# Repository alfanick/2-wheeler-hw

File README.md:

# TwoWheeler
TwoWheeler is Self Balancing Robot implemented using [XMOS startKIT](http://www.xmos.com/startkit) platform.

The robot is solving physical problem of inverted pendulum using PID regulator connecting motors with accelerometer. However its hardware design has much more features:
* 8 core 32-bit microcontroller
* bluetooth transceiver
* two distance meters
* motor driver with current sensing
* buck converter designed for use with LiPo battery
* battery voltage monitoring
* Over-The-Air parameters programming to built-in flash
* high torque motors with encoders

## Parts

* XMOS firmware - more in [balancer README](sw_twowheeler/app_balancer/README.md)
* computer app - API available in Ruby and console command interface with scripting (more in [documentation](ruby_twowheeler/README.md))
* circuit schematic and PCB design
* hardware design - not yet documented

## Authors

* Amadeusz Juskowiak - amadeusz@me.com
* Piotr Żurkowski  - kareth92@gmail.com

Inspired by Embedded Systems course at Poznan University of
Technology.

## License

*Copyright 2014 Amadeusz Juskowiak*

Licensed under the Apache License, Version 2.0 (the "License");
you may not use this file except in compliance with the License.
You may obtain a copy of the License at http://www.apache.org/licenses/LICENSE-2.0

Unless required by applicable law or agreed to in writing, software
distributed under the License is distributed on an "AS IS" BASIS,
WITHOUT WARRANTIES OR CONDITIONS OF ANY KIND, either express or implied.
See the License for the specific language governing permissions and
limitations under the License.

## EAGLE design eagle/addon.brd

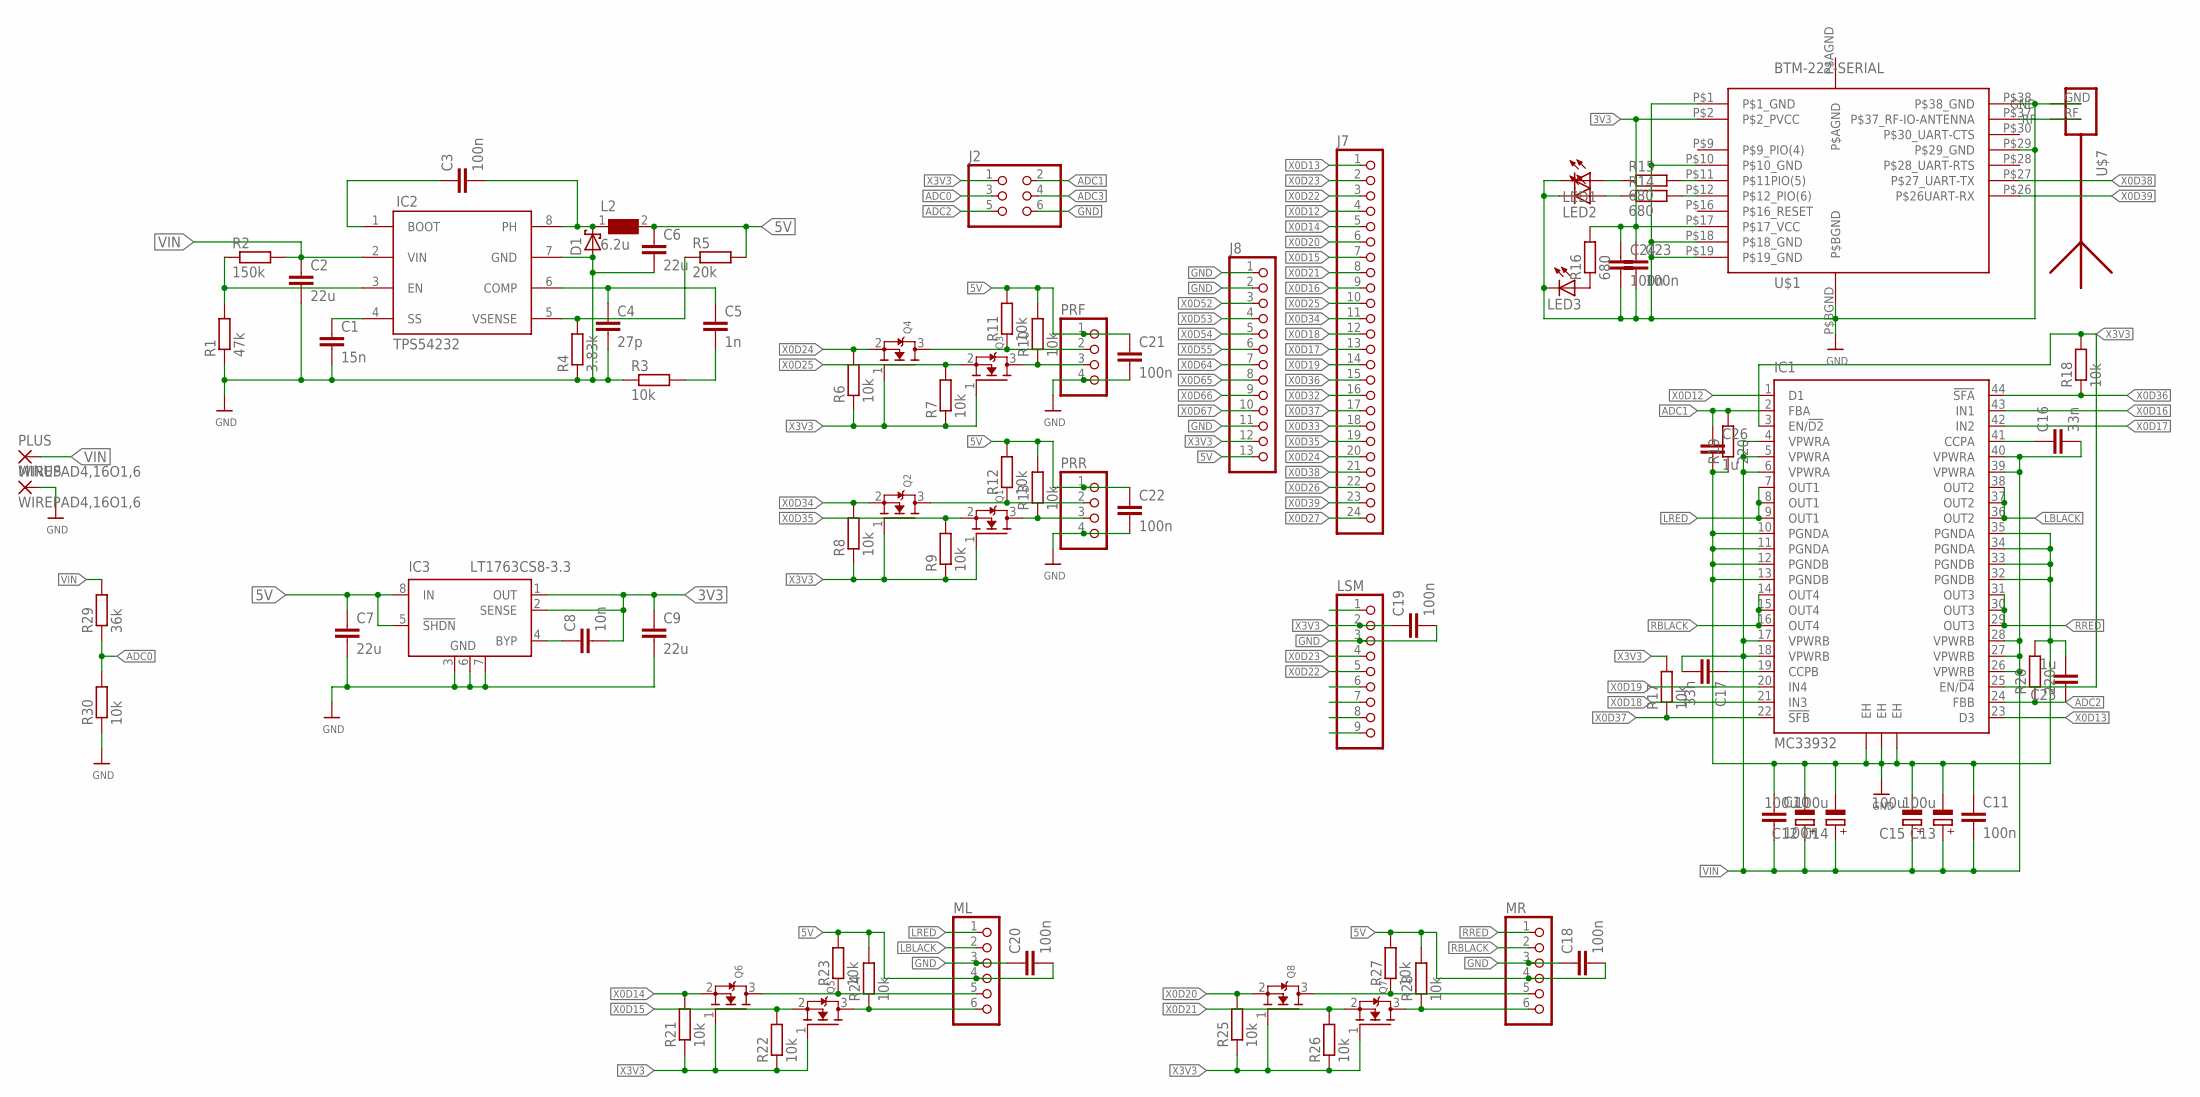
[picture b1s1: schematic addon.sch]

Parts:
C1: 15n; C0603
C2: 22u; C1210
C3, C10, C11, C18, C19, C20, C21, C22, C23, C24: 100n; C0603
C4: 27p; C0603
C5: 1n; C0603
C6: 22u; C1206
C7, C9: 22u; C0603
C8: 10n; C0603
C12, C13, C14, C15: 100u; D/7343-31R
C16, C17: 33n; C0603
C25, C26: 1u; C0603
D1: SCHOTTKY-DIODESMD; SMB
IC1: MC33932; HSOP44
IC2: TPS54232; YOURITRONICS_SO8
IC3: LT1763CS8-3.3; SOIC8
J2: PINHD-2X3; 2X03
J7: PINHD-1X24; 1X24
J8: PINHD-1X13; 1X13
L2: 6.2u; EAGLELIBRARY_WUERTH_ELEKTRONIK_EISOS_VERSION_6_WE-TPC_6823
LED1, LED2, LED3: LEDCHIPLED_0603; CHIPLED_0603
LSM: PINHD-1X9; 1X09
MINUS: WIREPAD4,16O1,6; 4,16O1,6
ML: PINHD-1X6; 1X06
MR: PINHD-1X6; 1X06
PLUS: WIREPAD4,16O1,6; 4,16O1,6
PRF: PINHD-1X4; 1X04
PRR: PINHD-1X4; 1X04
Q1, Q2, Q3, Q4, Q5, Q6, Q7, Q8: MOSFET-NREFLOW; SOT23-R
R1: 47k; R0603
R2: 150k; R0603
R3, R6, R7, R8, R9, R10, R11, R12, R13, R17, R18, R21, R22, R23, R24, R25, R26, R27, R28, R30: 10k; R0603
R4: 3.83k; R0603
R5: 20k; R0603
R14, R15, R16: 680; R0603
R19, R20: 220; R0603
R29: 36k; R0603
U$1: BTM-222-SERIAL; BTM-222
U$7: ANTENNA_1RIGHT; SWRA117D_RIGHT

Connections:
3V3: C8.2, C9.1, C23.1, C24.1, IC3.1 (OUT), IC3.2 (SENSE), R16.2, U$1.P$2 (P$2_PVCC), U$1.P$17 (P$17_VCC)
5V: C6.1, C7.1, C18.2, C20.2, C21.1, C22.1, IC3.5 (!SHDN), IC3.8 (IN), J8.13, L2.2, ML.4, MR.4, PRF.1, PRR.1, R5.2, R10.2, R11.2, R12.2, R13.2, R23.2, R24.2, R27.2, R28.2
ADC0: J2.3, R29.1, R30.2
ADC1: C26.1, IC1.2 (FBA), J2.2, R19.2
ADC2: C25.1, IC1.24 (FBB), J2.5, R20.1
ADC3: J2.4
GND: C1.2, C2.2, C4.2, C6.2, C7.2, C9.2, C10.1, C11.1, C12.-, C13.-, C14.-, C15.-, C18.1, C19.2, C20.1, C21.2, C22.2, C23.2, C24.2, C25.2, C26.2, D1.A, IC1.10 (PGNDA), IC1.11 (PGNDA), IC1.12 (PGNDB), IC1.13 (PGNDB), IC1.32 (PGNDB), IC1.33 (PGNDB), IC1.34 (PGNDA), IC1.35 (PGNDA), IC1.EH@1 (EH), IC1.EH@2 (EH), IC1.EH@3 (EH), IC2.7 (GND), IC3.3 (GND), IC3.6 (GND), IC3.7 (GND), J2.6, J8.1, J8.2, J8.11, LED1.C, LED2.C, LED3.C, LSM.3, MINUS.1, ML.3, MR.3, PRF.4, PRR.4, R1.1, R3.1, R4.1, R19.1, R20.2, R30.1, U$1.P$1 (P$1_GND), U$1.P$10 (P$10_GND), U$1.P$18 (P$18_GND), U$1.P$19 (P$19_GND), U$1.P$29 (P$29_GND), U$1.P$38 (P$38_GND), U$1.P$BGND, U$7.GND
LBLACK: IC1.36 (OUT2), IC1.37 (OUT2), IC1.38 (OUT2), ML.2
LRED: IC1.7 (OUT1), IC1.8 (OUT1), IC1.9 (OUT1), ML.1
unnamed: IC2.3 (EN), R1.2, R2.1
unnamed: C8.1, IC3.4 (BYP)
unnamed: PRR.3, Q1.3 (D), R13.1
unnamed: C3.1, IC2.1 (BOOT)
unnamed: C3.2, D1.C, IC2.8 (PH), L2.1
unnamed: C1.1, IC2.4 (SS)
unnamed: PRR.2, Q2.3 (D), R12.1
unnamed: C4.1, C5.1, IC2.6 (COMP)
unnamed: PRF.3, Q3.3 (D), R10.1
unnamed: C5.2, R3.2
unnamed: IC2.5 (VSENSE), R4.2, R5.1
unnamed: PRF.2, Q4.3 (D), R11.1
unnamed: U$1.P$37 (P$37_RF-IO-ANTENNA), U$7.RF
unnamed: R15.2, U$1.P$11 (P$11PIO(5))
unnamed: R14.2, U$1.P$12 (P$12_PIO(6))
unnamed: LED1.A, R15.1
unnamed: LED2.A, R14.1
unnamed: LED3.A, R16.1
unnamed: C16.1, IC1.41 (CCPA)
unnamed: C17.1, IC1.19 (CCPB)
unnamed: ML.6, Q5.3 (D), R24.1
unnamed: ML.5, Q6.3 (D), R23.1
unnamed: MR.6, Q7.3 (D), R28.1
unnamed: MR.5, Q8.3 (D), R27.1
P$AGND: U$1.P$AGND
RBLACK: IC1.14 (OUT4), IC1.15 (OUT4), IC1.16 (OUT4), MR.2
RRED: IC1.29 (OUT3), IC1.30 (OUT3), IC1.31 (OUT3), MR.1
VIN: C2.1, C10.2, C11.2, C12.+, C13.+, C14.+, C15.+, C16.2, C17.2, IC1.4 (VPWRA), IC1.5 (VPWRA), IC1.6 (VPWRA), IC1.17 (VPWRB), IC1.18 (VPWRB), IC1.26 (VPWRB), IC1.27 (VPWRB), IC1.28 (VPWRB), IC1.39 (VPWRA), IC1.40 (VPWRA), IC2.2 (VIN), PLUS.1, R2.2, R29.2
X0D12: IC1.1 (D1), J7.4
X0D13: IC1.23 (D3), J7.1
X0D14: J7.5, Q6.2 (S), R21.2
X0D15: J7.7, Q5.2 (S), R22.2
X0D16: IC1.43 (IN1), J7.9
X0D17: IC1.42 (IN2), J7.13
X0D18: IC1.21 (IN3), J7.12
X0D19: IC1.20 (IN4), J7.14
X0D20: J7.6, Q8.2 (S), R25.2
X0D21: J7.8, Q7.2 (S), R26.2
X0D22: J7.3, LSM.5
X0D23: J7.2, LSM.4
X0D24: J7.20, Q4.2 (S), R6.2
X0D25: J7.10, Q3.2 (S), R7.2
X0D26: J7.22
X0D27: J7.24
X0D32: J7.16
X0D33: J7.18
X0D34: J7.11, Q2.2 (S), R8.2
X0D35: J7.19, Q1.2 (S), R9.2
X0D36: IC1.44 (!SFA), J7.15, R18.1
X0D37: IC1.22 (!SFB), J7.17, R17.1
X0D38: J7.21, U$1.P$27 (P$27_UART-TX)
X0D39: J7.23, U$1.P$26 (P$26UART-RX)
X0D52: J8.3
X0D53: J8.4
X0D54: J8.5
X0D55: J8.6
X0D64: J8.7
X0D65: J8.8
X0D66: J8.9
X0D67: J8.10
X3V3: C19.1, IC1.3 (EN/!D2), IC1.25 (EN/!D4), J2.1, J8.12, LSM.2, Q1.1 (G), Q2.1 (G), Q3.1 (G), Q4.1 (G), Q5.1 (G), Q6.1 (G), Q7.1 (G), Q8.1 (G), R6.1, R7.1, R8.1, R9.1, R17.2, R18.2, R21.1, R22.1, R25.1, R26.1

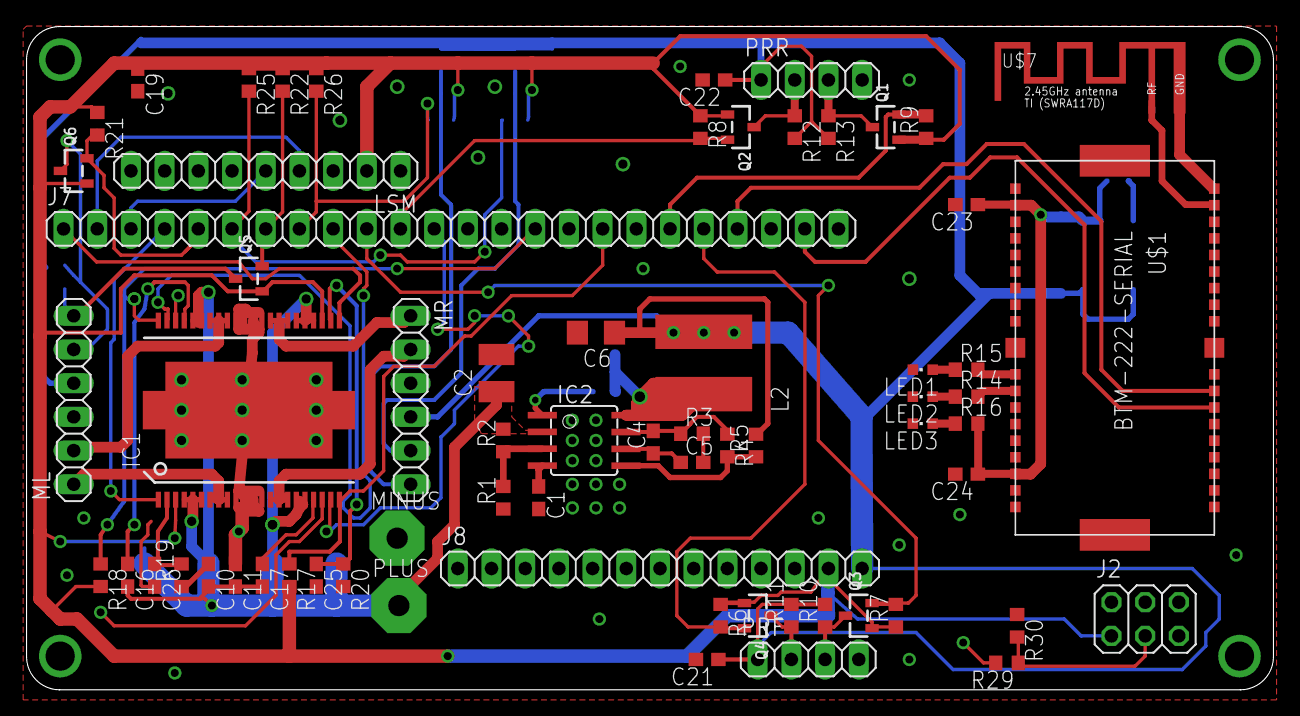
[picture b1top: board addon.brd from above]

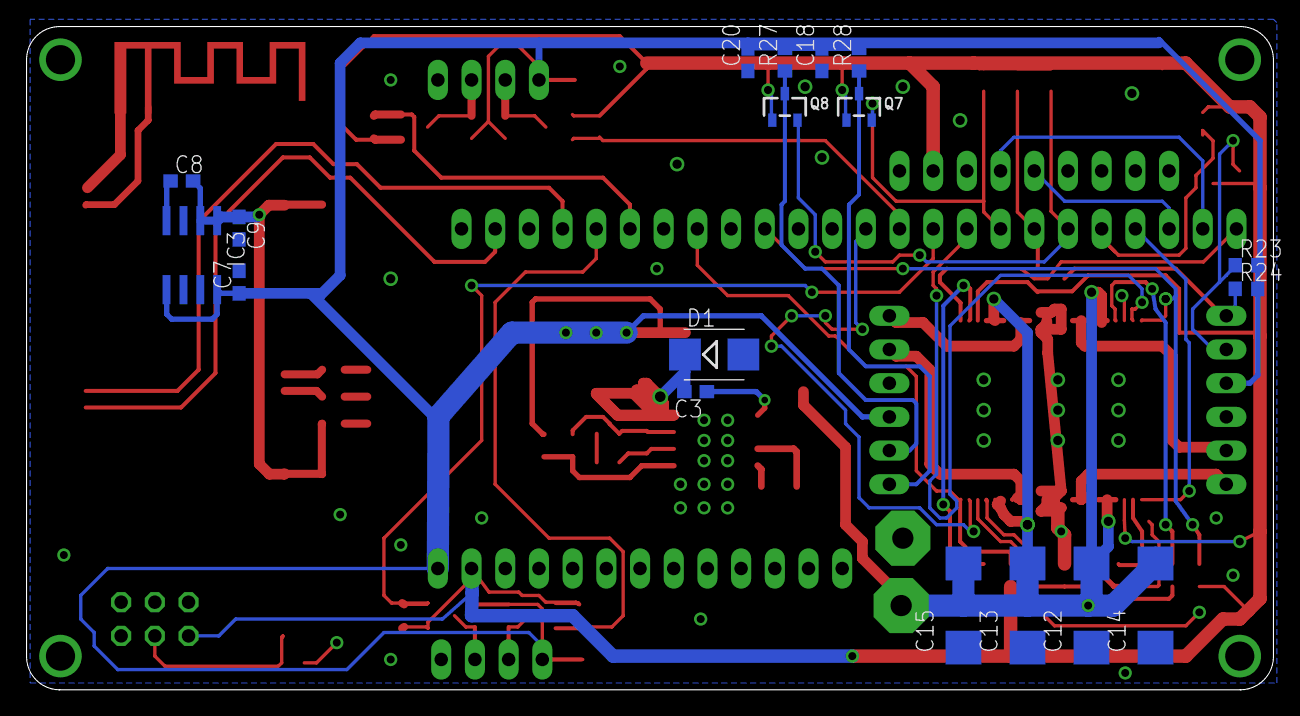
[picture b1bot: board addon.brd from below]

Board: 2 copper layers, 94.0 x 50.0 mm, 84 parts (18 on the bottom side), 56 nets.

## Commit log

2014-04-08 added template, added multithreaded led blinker
2014-04-09 added basic structure for pwm dc motor
2014-04-09 working PWM dc motor control
2014-04-09 removed bug - cound't stop when speed is 0
2014-04-09 combining motor tasks
2014-04-09 simplified syntax
2014-04-09 switching motor speed to check if pwm is implemented properly - everything is ok, yay
2014-04-09 testing stop
2014-04-09 decimal scale
2014-04-10 moved motors to module
2014-04-10 distance_sensor mock
2014-04-10 moved distance sensor as module
2014-04-10 probably working distance sensor module - with variable frequency
2014-04-10 usign guards, made combinable
2014-04-10 whitespaces
2014-04-10 unsigned
2014-04-10 guarding timer if freq is 0, moved calculation to read
2014-04-11 changed to hz
2014-04-11 better scaling to mm
2014-04-11 lower freq
2014-04-11 added accelometer lsm303d mock
2014-04-11 testing SPI
2014-04-11 trying to use built-in spi
2014-04-11 moved to i2c protocol, working accmag readings, no api
2014-04-11 removed faulty sync, benchmarking
2014-04-11 printing output
2014-04-12 cleaning code
2014-04-13 working on proper acc
2014-04-13 moved back to deb
2014-04-13 made combnable, simple median filter
2014-04-13 Cleaned out repo
2014-04-13 non overlapping freqs
2014-04-13 moved to debug_print instead of stdio
2014-04-13 made acc/mag combinable
2014-06-19 moved modules to git submodule, created platform config for 2wheeler
2014-06-19 added balancer app
2014-06-19 added bluetooth pins, probably wrong tx/rx
2014-06-19 removed struct, added lsm
2014-06-19 moved sensor structs to platform.h
2014-06-19 added board revision guards
2014-06-19 guards removed
2014-06-19 resttructurized code for viisblity
2014-06-19 udpatet to xtimecomposer13.10
2014-06-20 added motors
2014-06-20 new test
2014-06-20 added adc, not workign
2014-06-20 working adc
2014-06-20 added rx/tx uart, bluetooth testing
2014-06-20 basic
2014-06-21 cores
2014-06-21 readability
2014-06-21 Add missing modules
2014-06-21 Rotate
2014-06-21 added skeleton
2014-06-22 moved logic to seperate files
2014-06-22 added mock
2014-06-22 nice funtctional structure
2014-06-22 moved main to mbalancer
2014-06-24 motors movement
2014-06-24 gravity, sending acc
2014-06-24 naive alg
2014-06-24 greater freq
2014-06-24 naive almost wroking
2014-06-24 higher freq, emergency cut off
2014-06-24 two steps
2014-06-24 interfacing balancer
2014-06-24 working on pif
2014-06-25 increased pwm resolution, experimenting with pid
2014-07-01 testing hall
2014-07-01 added motors status observing
2014-07-02 added current sensing
2014-07-02 added overcurrent protection
2014-07-02 playing with pid consts
2014-07-02 calibrated battery indicator, uart setup
2014-07-02 bluetooth mock
2014-07-02 bluetooth is working
2014-07-02 testing not needed
2014-07-02 number senidng
2014-07-02 senidng battery voltage over bluetooth
2014-07-03 added commands glossary
2014-07-03 added readme to top level
2014-07-03 cmd change
2014-07-03 makefile for flashing without debug and scope, pid via bluetooth, commands, yay
2014-07-03 commands proper order
2014-07-03 added run and flash targets to makefile, VER? command with git commit id
2014-07-03 added ver to readme, formal response
2014-07-03 formal voltage output
2014-07-03 added picocom command for connection with 2hw
2014-07-03 added RPM command
2014-07-03 added angle commands
2014-07-03 removed balancing guard - moved it inside, so angle is updated
2014-07-03 disabled autostart
2014-07-03 removed bug - not updating timer when breaking balancing
2014-07-03 no delay in bluetooth send
2014-07-03 breaking loop
2014-07-03 refactored directory structure
2014-07-03 added eagle files
2014-07-03 added Apache License
2014-07-03 license
2014-07-03 added proper readme
2014-07-03 authors
2014-07-03 words
2014-07-03 added target calibration command
2014-07-03 angle not target
2014-07-03 letter
2014-07-04 added ruby api
2014-07-04 Ki and Kd depandant on sample time
2014-07-04 added console spawner
2014-07-04 changed pid coeffs to morelike balancing, made balancer.rb executable
2014-07-04 more minimal console
2014-07-04 testing filters
2014-07-04 added logging
2014-07-04 using builtin history to save comamnds
2014-07-04 testing pwm freq
2014-07-04 slowed downspi clock
2014-07-04 enabled by default
2014-07-04 experimenting with pwm from xmos, not enough resources :(
2014-07-04 enw branch in modules
2014-07-04 timing
2014-07-04 derivative kick
2014-07-04 integrating error
2014-07-04 clampign integral
2014-07-04 moved pid to function
2014-07-04 added looptime
2014-07-04 sending looptime over bluetooth in full scale
2014-07-04 beautiful rounding
2014-07-05 new pid, target
2014-07-05 1khz pwm freq
2014-07-05 removed filter - does not working, ggyro required, moved stopping when critical angle to safety;
2014-07-05 removed bug, stopping with tags
2014-07-05 added simple lowpass filter to angle
2014-07-05 new pid coeefs
2014-07-06 moved lowpass and pitch to lsm
2014-07-06 new pid
2014-07-06 added lowpass chart, scaling
2014-07-06 added alp command for lowpass filter parameter
2014-07-06 added lowpass filter setting based on delay
2014-07-06 added setting lowpass filter based on cutoff frequency, added aliases for self
2014-07-06 scripts loading i.e. config
2014-07-06 balancing, lower delay
2014-07-06 added alp to readme
2014-07-06 added info about api
2014-07-06 multiple settings including, fail messages
2014-07-06 removed bug - requiring first only
2014-07-06 renamed settings to smooth, added shortnames
2014-07-06 more aliases
2014-07-07 renamed sample time to loop delay, setting loop delay over the air
2014-07-07 nicer look
2014-07-07 refactored main loo
2014-07-07 added current reading
2014-07-07 added lowpass filters to current and battery adc
2014-07-07 more responsive current adc
2014-07-07 added readme to ruby
2014-07-07 added github command which creates link to commit with last version
2014-07-07 linked readmes to docs
2014-07-07 more note
2014-07-07 almost standing still
2014-07-07 added some description
2014-07-08 added gui mockup based on qt4
2014-07-08 moved speed boost to pid, made speed threshold and boost accesible over bluetooth
2014-07-08 new synonyms and pid
2014-07-08 delay removed from lsm
2014-07-08 metaprogramming - creating methods instead of aliasing missing methods, so pry autocomplete works
2014-07-08 added sample gathering, lowpass on pid
2014-07-09 added pid_lowpass commands
2014-07-09 removed bug, sending wrong response
2014-07-09 removed speed aliases - motors should be used, made synonyms of self readonly
2014-07-09 added flashproxy mock - it will save values pernamently to flash
2014-07-11 added module config, formatting data partition
2014-07-11 removed gui
2014-07-11 added adc lock mock
2014-07-11 spinoff of startkit adc
2014-07-11 working releasing and acquiring adc port for flash/adc - still need to do config_open
2014-07-11 sending error while already in FLASH mode
2014-07-11 added flash command to readme
2014-07-11 aliases to self
2014-07-11 added flash reading and writign when flash flag is set, ofc not wokring yet, because of these pointers
2014-07-11 changed syntax
2014-07-13 added gui mockup from qtdesigner
2014-07-14 moved to unsafe pointers
2014-07-15 debugging flash
2014-07-16 redone unsafe pointers, working flash AND adc
2014-07-16 forgot to inlcude asser t moduel
2014-07-16 disabling adc completely
2014-07-16 reading settings from flash
2014-07-16 added flash global var
2014-07-16 added subscript operator
2014-07-16 added flash support to readme
2014-07-16 unified command wiht page buffer
2014-07-16 added default values
2014-07-16 removed random values bug
2014-07-16 syntactic sugar
2014-07-17 optimized config reading and saving
2014-07-17 added multiple flash operation comd
2015-04-20 style
2015-04-21 using moving to imu module
2015-04-21 saving settings
2015-04-22 gyro test
2015-04-22 kalman stub
2015-04-23 moved kalman
2015-04-23 testing kalman
2015-04-23 better dt
2015-04-23 safety
2015-04-24 kalman disable/enable

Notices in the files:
parts and their libraries:
microbuilder: This work is placed in the public domain, and may be freely used for commercial and non-commercial work with the following conditions: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
